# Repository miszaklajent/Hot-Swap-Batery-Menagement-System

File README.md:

# Alizka power management system

## założenia
- modułowy system
- możliwość instalacji od 1 do 4 baterii
- redundancja baterii
- zabezpieczenie nadmiernego rozładowania baterii
- rozładowuje wszystkie podłączone baterie po kolei, w kolejności od najbardziej rozładowanej do najbardziej naładowanej.
- w trakcie działania przekazuje moc podłączonych baterii w sposób nie przerwany
- pozwala na przesył do 400W mocy (25A 16V przy prawie rozładowanej baterii)

## działanie 

### Załączenie:
1. Podczas pierwszego załączenia system wybiera najbardziej rozładowaną baterię, której napięcie przekracza minimalny poziom napięcia
2. System wykonuje soft-start aby ograniczyć prąd ładowania pojemności wyjściowej.
3. Zwiększanie wypełnienia przebiegu sterującego układem przetwornicy, do momentu osiągnięcia pracy ciągłej górnego tranzystora.

### Praca ciągła:
1. Podczas pracy ciągłej, przetwornica modułu baterii która aktualnie jest wykorzystywana, ma na stałe załączony górny tranzystor.
2. Praca ciągła trwa do momentu kiedy:
    - Napięcie na aktualnie wykorzystywanej baterii spadnie poniżej napięcia minimalnego
    - Bateria aktualnie wykorzystywana zostanie odłączona

### Przełączenie baterii:
1. Przed przełączeniem, system wybiera jedną z pozostałych baterii, na którą zaraz się przełączy. Będzie to następna bateria o najniższym napięciu, ale przekraczającym napięcie minimalne.
2. Przetwornica baterii wybranej do przełączenia jako następna, cały czas kluczuje w trybie stand-by (jej wyjście jest aktywnie ustalone na poziomie ok 100mV poniżej aktualnego wyjścia działającej baterii przez mikrokontroler)
3. Podczas przełączenia, przetwornica baterii o wyższym napięciu, zaczyna zwiększać wypełnienie do momentu osiągnięcia pełnego wypełnienia.
4. Podczas zwiększania wypełnienia przetwornicy baterii o wyższym napięciu, układ diody idealnej zawarty za wyjściem przetwornicy zapobiegnie przepływaniu prądów wyrównawczych.
5. Przypadku nagłego wypięcia baterii, diody idealne automatycznie przełączając tor mocy w taki sposób, aby moc była pobierana z przetwornicy która była w trybie stand-by, co powoduje jedynie nieznaczne obniżenie napięcia wyjścia. Po wykryciu odłączenia, mikrokontroler podnosi wypełnienie sygnału sterującego tak jak w punkcie wyżej.

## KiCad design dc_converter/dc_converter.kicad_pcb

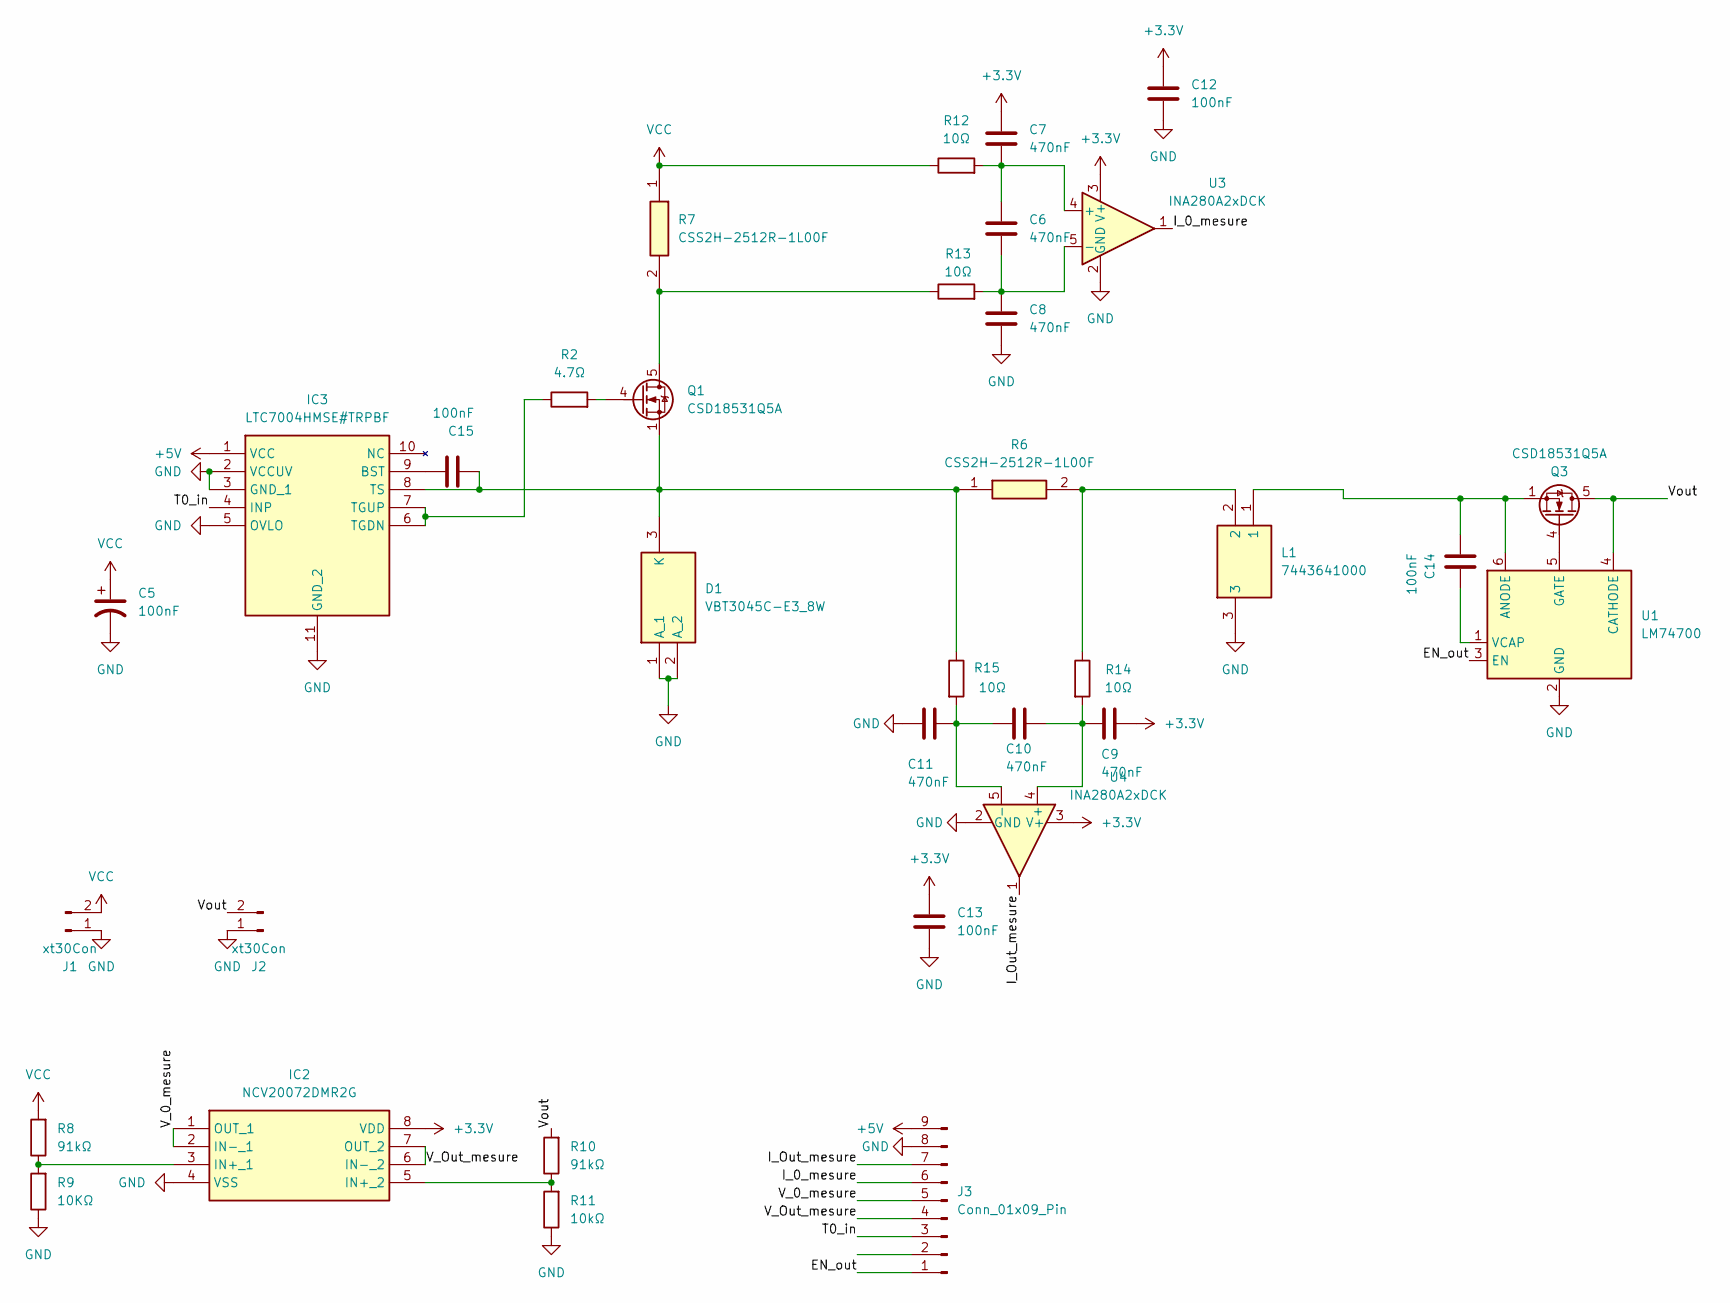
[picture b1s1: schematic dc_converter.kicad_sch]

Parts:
C5: 100nF
C6, C7, C8, C9, C10, C11: 470nF; C_0402_1005Metric
C12, C13, C14, C15: 100nF; C_0402_1005Metric
D1: VBT3045C-E3_8W; TO-263AB_1; Mouser Part Number 625-VBT3045C-E3/8W
IC2: NCV20072DMR2G; SOP65P490X110-8N; Mouser Part Number 863-NCV20072DMR2G
IC3: LTC7004HMSE#TRPBF; SOP50P490X110-11N; Mouser Part Number 584-7004HMSETRPBF
J1, J2: xt30Con; AMASS_XT30U-M_1x02_P5.0mm_Vertical
J3: Conn_01x09_Pin; JST_GH_SM09B-GHS-TB_1x09-1MP_P1.25mm_Horizontal
L1: 7443641000; WE-HCF_SMD_HIGH-CURRENT_INDUCTOR; Mouser Part Number 710-7443641000
Q1, Q3: CSD18531Q5A; TDSON-8-1
R2: 4.7Ω; R_1206_3216Metric_Pad1.30x1.75mm_HandSolder
R6, R7: CSS2H-2512R-1L00F; RESC6430X87N; Mouser Part Number 652-CSS2H2512R1L00F
R8, R10: 91kΩ; R_0402_1005Metric
R9: 10KΩ; R_0402_1005Metric
R11: 10kΩ; R_0402_1005Metric
R12, R13, R14, R15: 10Ω; R_0402_1005Metric
U1: LM74700; SOT-23-6
U3, U4: INA280A2xDCK; SOT-353_SC-70-5

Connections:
+3.3V: C7.2, C9.2, C12.2, C13.2, IC2.8 (VDD), U3.3 (V+), U4.3 (V+)
+5V: IC3.1 (VCC), J3.9
/EN_out: J3.1, U1.3 (EN)
/I_0_mesure: J3.6, U3.1
/I_Out_mesure: J3.7, U4.1
/T0_in: IC3.4 (INP), J3.3
/V_0_mesure: IC2.1 (OUT_1), IC2.2 (IN-_1), J3.5
/V_Out_mesure: IC2.6 (IN-_2), IC2.7 (OUT_2), J3.4
/Vout: J2.2, Q3.5 (D), R10.2, U1.4 (CATHODE)
GND: C5.2, C8.1, C11.1, C12.1, C13.1, D1.1 (A_1), D1.2 (A_2), IC2.4 (VSS), IC3.2 (VCCUV), IC3.3 (GND_1), IC3.5 (OVLO), IC3.11 (GND_2), J1.1, J2.1, J3.8, L1.3, R9.1, R11.1, U1.2 (GND), U3.2 (GND), U4.2 (GND)
unnamed: C15.1, D1.3 (K), IC3.8 (TS), Q1.1 (S), Q1.2 (S), Q1.3 (S), R6.1, R15.1
unnamed: IC2.3 (IN+_1), R8.1, R9.2
unnamed: IC2.5 (IN+_2), R10.1, R11.2
unnamed: C15.2, IC3.9 (BST)
unnamed: IC3.6 (TGDN), IC3.7 (TGUP), R2.1
unnamed: L1.2, R6.2, R14.1
unnamed: Q1.5 (D), R7.2, R13.1
unnamed: Q1.4 (G), R2.2
unnamed: Q3.4 (G), U1.5 (GATE)
unnamed: C14.1, L1.1, Q3.1 (S), Q3.2 (S), Q3.3 (S), U1.6 (ANODE)
unnamed: C14.2, U1.1 (VCAP)
unnamed: C6.2, C7.1, R12.2, U3.4 (+)
unnamed: C6.1, C8.2, R13.2, U3.5 (-)
unnamed: C9.1, C10.2, R14.2, U4.4 (+)
unnamed: C10.1, C11.2, R15.2, U4.5 (-)
VCC: C5.1, J1.2, R7.1, R8.2, R12.1

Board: 2 copper layers, 33 parts (0 on the bottom side), 26 nets, no tracks yet.
